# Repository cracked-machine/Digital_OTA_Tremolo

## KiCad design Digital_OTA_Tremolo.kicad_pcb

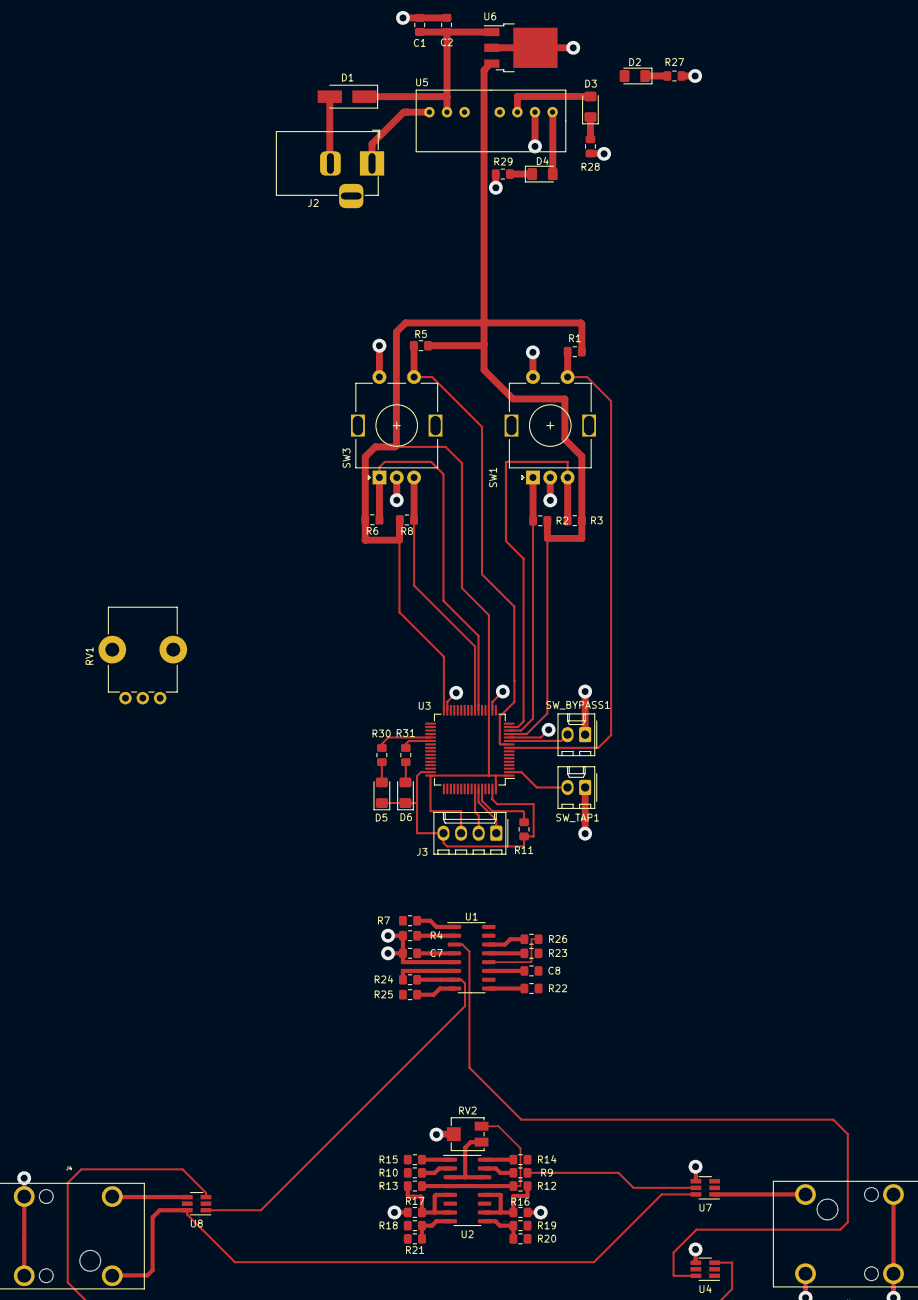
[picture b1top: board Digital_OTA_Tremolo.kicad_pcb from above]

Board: 2 copper layers, 59 parts (0 on the bottom side), 52 nets.

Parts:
C1: 10uF; C_0805_2012Metric_Pad1.15x1.40mm_HandSolder
C2, C7, C8: 100nF; C_0805_2012Metric_Pad1.15x1.40mm_HandSolder
D1: D_Schottky; D_SMA_Handsoldering
D2, D3, D4, D5, D6: LED; LED_1206_3216Metric_Pad1.42x1.75mm_HandSolder
J1, J4: NRJ6HM-1-PRE; NRJxHx
J2: Barrel_Jack_Switch; BarrelJack_Horizontal
J3: Conn_01x04; Molex_KK-254_AE-6410-04A_1x04_P2.54mm_Vertical
R1, R2, R3, R5, R6, R8, R9, R10, R11, R12, R13, R25, R26: 10K; R_0805_2012Metric_Pad1.15x1.40mm_HandSolder
R4: 10k; R_0805_2012Metric_Pad1.15x1.40mm_HandSolder
R7, R18, R19: 4K7; R_0805_2012Metric_Pad1.15x1.40mm_HandSolder
R14, R15, R16, R17: 33K; R_0805_2012Metric_Pad1.15x1.40mm_HandSolder
R20, R21, R24, R27, R28, R29, R30, R31: 1K; R_0805_2012Metric_Pad1.15x1.40mm_HandSolder
R22, R23: 2K7; R_0805_2012Metric_Pad1.15x1.40mm_HandSolder
RV1: B10K; Potentiometer_Bourns_PTV09A-1_Single_Vertical
RV2: 1K; Potentiometer_Bourns_3314J_Vertical
SW1, SW3: Rotary_Encoder_Switch; RotaryEncoder_Alps_EC11E-Switch_Vertical_H20mm
SW_BYPASS1: SW_SPST; Molex_KK-254_AE-6410-02A_1x02_P2.54mm_Vertical
SW_TAP1: SW_SPST; Molex_KK-254_AE-6410-02A_1x02_P2.54mm_Vertical
U1: TL074; SOIC-16_3.9x9.9mm_P1.27mm
U2: LM13700; SOIC-16_3.9x9.9mm_P1.27mm
U3: STM32F072RBTx; LQFP-64_10x10mm_P0.5mm
U4, U7, U8: DG468DV_T1_E3; SOT-23-6_Handsoldering
U5: RS6-0515D; RS6
U6: NCV5501_DT33RKG; TO-252-3_TabPin2

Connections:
+3V3: D2.2, J3.3, R1.2, R2.2, R3.2, R5.2, R6.2, R8.2, U3.1, U3.13, U3.19, U3.32, U3.48, U3.64, U6.3
+15V: C7.1, D3.2, R9.2, R10.2, U1.4, U2.11, U4.5, U5.6, U7.5, U8.5
-15V: C8.1, D4.2, R18.1, R19.1, U1.11, U2.6, U4.2, U5.8, U7.2, U8.2
/CV1: R22.2, U3.20
/CV2: R23.2, U3.21
/DISPLAY_I2C1_SCL: J3.2, U3.58
/DISPLAY_I2C1_SDA: J3.1, U3.59
/INV_CV1: R14.1, R25.1, U1.8
/INV_CV2: R15.1, R26.1, U1.14
/InvertInput: R7.2, R12.2, R13.2, RV2.3, U2.4, U2.13
/NonInvInput: RV2.1, U2.3, U2.14
/PowerSupply/+VIN: D1.2, J2.2
/PowerSupply/-VIN: J2.1, U5.1
/SINE1_LED: R30.2, U3.37
/SINE1_TAPTEMPO_EXTI13: SW_TAP1.2, U3.2
/SINE1_TOGGLE_EXTI1: R1.1, SW1.S1, U3.9
/SINE2_LED: R31.2, U3.38
/SINE2_TOGGLE_EXTI2: R5.1, SW3.S1, U3.10
/SW_BYPASS_EXTI3: SW_BYPASS1.2, U3.11
/SW_CLOSE_BYPASS: U3.25, U7.3
/SW_CLOSE_FX: U3.24, U4.3, U8.3
/TIM2_CH1_ENCODER1: R2.1, SW1.A, U3.14
/TIM2_CH2_ENCODER1: R3.1, SW1.B, U3.15
/TIM3_CH1_ENCODER2: R6.1, SW3.A, U3.22
/TIM3_CH2_ENCODER2: R8.1, SW3.B, U3.23
unnamed: C1.1, C2.1, D1.1, U5.2, U6.1
unnamed: D2.1, R27.1
unnamed: D3.1, R28.1
unnamed: D4.1, R29.1
unnamed: D5.2, R30.1
unnamed: D6.2, R31.1
unnamed: J1.1, U4.1, U7.1
unnamed: J4.1, U7.6, U8.6
unnamed: R4.1, RV1.3, U1.2
unnamed: R7.1, RV1.1, RV1.2, U1.1
unnamed: R9.1, U2.15
unnamed: R10.1, U2.2
unnamed: R11.1, U3.60
unnamed: R12.1, R16.2, U2.10, U2.12
unnamed: R13.1, R17.2, U2.5, U2.7
unnamed: R14.2, U2.16
unnamed: R15.2, U2.1
unnamed: R18.2, R21.1, U2.8
unnamed: R19.2, R20.1, U2.9
unnamed: R20.2, R21.2, R24.1, U1.6
unnamed: R22.1, U1.9
unnamed: R23.1, U1.13
unnamed: R24.2, U1.7, U8.1
unnamed: R25.2, U1.10
unnamed: R26.2, U1.12
unnamed: U1.3, U4.6
VCOM: C1.2, C2.2, C7.2, C8.2, D5.1, D6.1, J1.2, J1.3, J1.4, J3.4, J4.2, J4.3, J4.4, R4.2, R11.2, R16.1, R17.1, R27.2, R28.2, R29.2, RV2.2, SW1.C, SW1.S2, SW3.C, SW3.S2, SW_BYPASS1.1, SW_TAP1.1, U1.5, U3.12, U3.18, U3.31, U3.47, U3.63, U4.4, U5.7, U6.2, U7.4, U8.4

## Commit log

2020-03-17 updated schema design
2020-03-20 updated schema
    _ added controls
2020-03-20 Updated power supply section
2020-03-22 Updated RevA design
2020-03-24 Added switching mechanism
